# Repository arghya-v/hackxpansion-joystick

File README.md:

# hackxpansion-joystick

The joystick module for hackxpansion!
The module uses a two-axis potentiometer joystick to provide X and Y analog readings, allowing projects to interpret directional movement and user input. The center button adds an extra digital input for selection or other interactions.
<br/>
**Crates:** pkg:cargo/JoystickHackx@0.1.0
# Images

### Pin Mapping

| Function      | Xpanse GPIO  |
| ------------- | ------------ |
| X axis        | GPIO7 / ADC0 |
| Y axis        | GPIO8 / ADC1 |
| Center button | GPIO9        |

See the [Xpanse API docs](https://docs.rs/xpanse-api/latest/xpanse_api/index.html)

The joystick axes are connected as potentiometers between 3.3 V and GND, with their wipers connected to the ADC pins. This allows the X and Y positions to be read as analog voltage levels. The center button provides a digital input.

## BOM
| Designator | Footprint                  | Quantity | Value           | LCSC Part # | Price (CAD) |
| ---------- | -------------------------- | -------- | --------------- | ----------- | ----------- |
| C1, C2     | C338148_C0402              | 2        | 47nF            | C338148     | $0.08       |
| J1         | Male_Module                | 1        | Included in kit | —           | —           |
| R1         | 0805                       | 1        | 1k1             | C185294     | $1.00       |
| R2         | 0805                       | 1        | 1k2             | C269531     | $1.00       |
| VR1        | C918854_SW-TH_RKJXV1224005 | 1        | RKJXV122400R    | C918854     | $2.64       |
| PCB        | —                          | —        | PCB             | —           | $4.00       |
| PCBA Fee   | —                          | —        | PCBA Assembly   | —           | $18.26      |
| Shipping   | —                          | —        | Shipping        | —           | $6.45       |
| TOTAL      | —                          | —        | —               | —           | $33.43      |
---

This was all possible thanks to [Hackspansion: A hackclub YSWS](http://hackxpansion.hackclub.com/)

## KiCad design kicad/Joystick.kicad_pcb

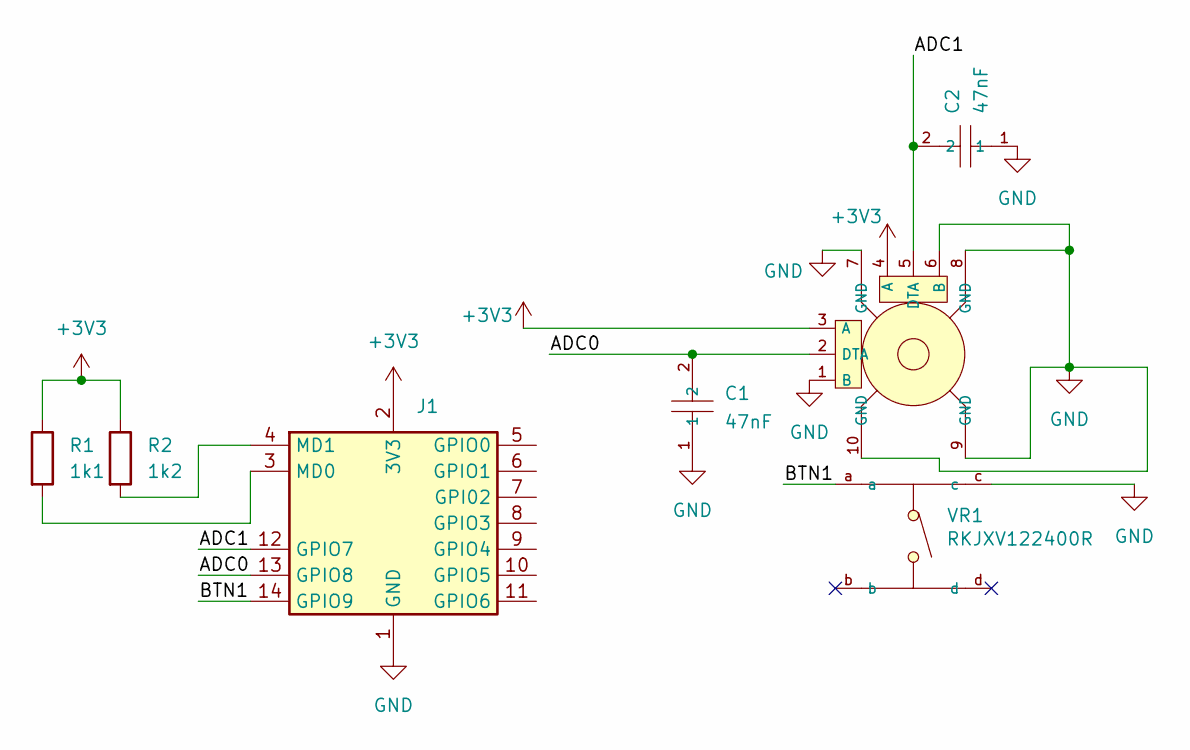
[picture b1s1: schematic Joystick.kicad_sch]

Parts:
C1, C2: 47nF; C338148_C0402; LCSC C338148
J1: Male_Module
R1: 1k1; R_0805_2012Metric_Pad1.20x1.40mm_HandSolder
R2: 1k2; R_0805_2012Metric_Pad1.20x1.40mm_HandSolder
VR1: RKJXV122400R; C918854_SW-TH_RKJXV1224005; LCSC C918854

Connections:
+3V3: J1.2 (3V3), R1.1, R2.1, VR1.3 (A), VR1.4 (A)
/ADC0: C1.2, J1.13 (GPIO8), VR1.2 (DTA)
/ADC1: C2.2, J1.12 (GPIO7), VR1.5 (DTA)
/BTN1: J1.14 (GPIO9), VR1.a
GND: C1.1, C2.1, J1.1 (GND), VR1.1 (B), VR1.6 (B), VR1.7 (GND), VR1.8 (GND), VR1.9 (GND), VR1.10 (GND), VR1.c
unnamed: J1.3 (MD0), R1.2
unnamed: J1.4 (MD1), R2.2

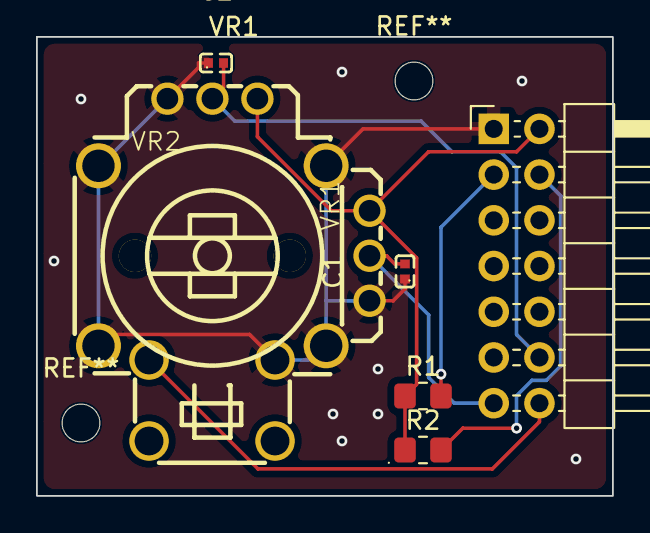
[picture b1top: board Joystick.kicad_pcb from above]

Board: 2 copper layers, 32.0 x 25.5 mm, 6 parts (0 on the bottom side), 7 nets.

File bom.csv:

Designator,Footprint,Quantity,Value,LCSC Part #,Price (CAD)
"C1, C2",C338148_C0402,2,47nF,C338148,0.08
J1,Male_Module,1,Included in kit,,
R1,0805,1,1k1,C185294,1.00
R2,0805,1,1k2,C269531,1.00
VR1,C918854_SW-TH_RKJXV1224005,1,RKJXV122400R,C918854,2.64
PCB,,,PCB,,$4.00
PCBA Fee,,,PCBA Assembly,,$18.26
Shipping,,,Shipping,,$6.45
TOTAL,,,,,$33.43
